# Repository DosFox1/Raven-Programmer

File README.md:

# Raven-Programmer
An implementation of a 68HC705E1 Programmer, to replace the 68HC05E1 Mask ROM Microcontroller that was used as the EGRET and CUDA ICs in 90s Macintoshes, with the EPROM programmable 68HC705E1 part. 

The EGRET and CUDA were used to implement the RTC, PRAM, Soft Power and other functions. As these are located near to the RTC battery, these are well known to be destroyed either by battery leaks or due to capacitor leaks.

The EGRET replacement has been confirmed to work. Many thanks to Max1zzz for testing them.

# How do I use it?

Unfortunately, the programmer is a two step process.
 The first step is to program the desired ROM to a suitable 2764 compatible 8K E/EPROM, using a suitable programmer. (In my case, I used an AT28C64 with a TI866+).

Once programmed, the ROM and a blank 68HC705e1 can then be inserted into the Raven programmer.

First, set switch 1 to on, and switch 2 to off. 
This will set the programmer into “validation” mode.
Bring the 5v rail up first before bringing the 16v programming rail up. 
Bringing the 16v rail up before the 5v rail may result in damage tom the IC. 
When both rails are stable, hit the reset button. 
Note that the 68HC705 will not enter boot loader mode until both power rails are present.

If the device has not been programmed before, neither the program or verify LEDs will light. 

Once satisfied that the 68HC705e1 is likely to be unprogrammed, set both switch 1 and 2 to “on”, and hit the reset button. 
This will set the programmer into program mode. 
At this point, the programmer will begin copying the contents of the external ROM into the onboard ROM of the 68HC705e1.
During this, the “program” LED will become illuminated. 
This process should take approximately 40 seconds, wherein the “program” LED will be extinguished, and the “verify” LED will become illuminated - to indicate that programming was successful.
If there is an issue - the “verify” LED will not become illuminated. 

To ensure that programming was a success, power cycle the setup (whilst ensuring that the 16v rail is powered down first, and powered up first), and set switch 1 to “on” and switch 2 to “off”. 
Again, this will set the programmer into verify mode - however, when the reset LED is hit in this instant, the “verify” LED should become illuminated after a second. 

Once satisfied, power down the programmer, and remove the 68HC705. 

# Where do I get the ROMs? 
At the moment, there is only a single ROM available in the correct format for the Raven programmer. This is the 341S0851 EGRET, that is a commonly used replacement for the majority of the EGRETs. 

The original program data was taken from the internet archive: 
https://archive.org/details/macroms

Which is likely taken from this tool here for dumping EGRET/CUDA ROMs:
https://www.gryphel.com/c/minivmac/extras/egretrom/

These ROMs have been used with a 68HC05 emulator within MAME, so it is likely the data is valid data. 

However, please note that there is some formatting that needs to take place before the ROM files can be burnt to the external 8K EPROM. 

Namely, the program data needs to be offset from 0x0000 to 0x0F00. This program data is 4096 bytes long, and resides from 0x0F00 to 0x1EFF. 

Following this, there needs to be single byte written at 0x1F00 - which is the Mask Option Register. 
From what we can tell, this data is usually part of the mask of the 68HC05e1 itself, and as a result needs to be defined in the 68HC705. As the data from 0x1F00 through to 0x1FEF is the bootloader ROM on the 68HC05e1, and the dumps include the entire bootloader ROM for the EGRET and CUDA, then writing the data from 0x1F00 from the dump will not work. 
Instead, MOR needs to be defined from context clues. 

The MOR defines three things - whether the watchdog is enable, if an external interrupt is enabled, and the rate of the internal interrupt.
In the case of the EGRET, the NMI pin is always held high - meaning it’s likely the external interrupt is not used. According to a decompilation by PhilPem, the Watchdog timer is not used. 
As the EGRET is also used as an RTC, it’s likely that the internal interrupt is 1s long. As a result, 0x1F00 should have the byte “0x04” written to it.

It’s hoped that even if the internal interrupt is wrong, then the clock will just run slightly slow - which can be easily fixed by burning a new EGRET. 

The data from 0x1F01 through to 0x1FEF should then be set to 0x00, as this is the region where the bootloader resides. It’s safer to null out this data region to avoid possibly corrupting the 68hc705e1. 

Finally, the last 16 bytes from 0x1FF0 through to 0x1FFF are the EPROM user vectors, that need to be copied from the original ROM. 

Additionally, there is an errata sheet (included) that details a bug with the exact mask version of the 68HC705 that I have programmed (D32N). Basically a silicon bug means that the 68HC705e1 doesn’t read the data at 0x1000, and reads the data at 0x0000 for a single cycle. This is why the included example ROM has a single byte of 0x12 at 0x0000 - this is a duplication of the data at 0x1000. It does not harm or hinder to have this additional byte present at 0x0000. 

Additional correctly formatted ROMs will be added if and when they are needed. 
Contact me directly for a specific ROM.

# Errata
VDEV2 is the current version of the Raven Programmer. The VDEV1 version had two issues - one introduced by me, the other by NXP. 
The issue I managed to introduce was accidentally mislabelling R1 and R2. I managed to get the 330K and 20M labels the wrong way around. This resulted in the oscillator not running, and was fixed in VDEV2. 

The major issue was introduced by NXP, who in their datasheet (68hc705e1.pdf in the datasheet folder) failed to mention that PB1 needed to be brought high to 5v, and PB6/PB7 needed to be brought low to 0v. As a result, with those three pins floating, the 68HC705e1 behaved erratically and failed to program. In this instant, both the verify and program LEDs remained illuminated.

Thankfully, the discovery of the original Motorola datasheet (68HC705e1 Better Datasheet.pdf), I was able to correct the issue, and actually program the devices.

# Acknowledgements 

Many thanks to PhilPem (@philpem@digipres.club) for helping with the software side of this headache, hopefully they work!

Also many thanks must be given to Max1zzz (https://github.com/max234252/) for agreeing to testing this new batch of EGRETs. We can only help that these will work, as well as agreeing to send an OTP CUDA over, so we can hopefully have a look at what a proper MOR byte should look like!

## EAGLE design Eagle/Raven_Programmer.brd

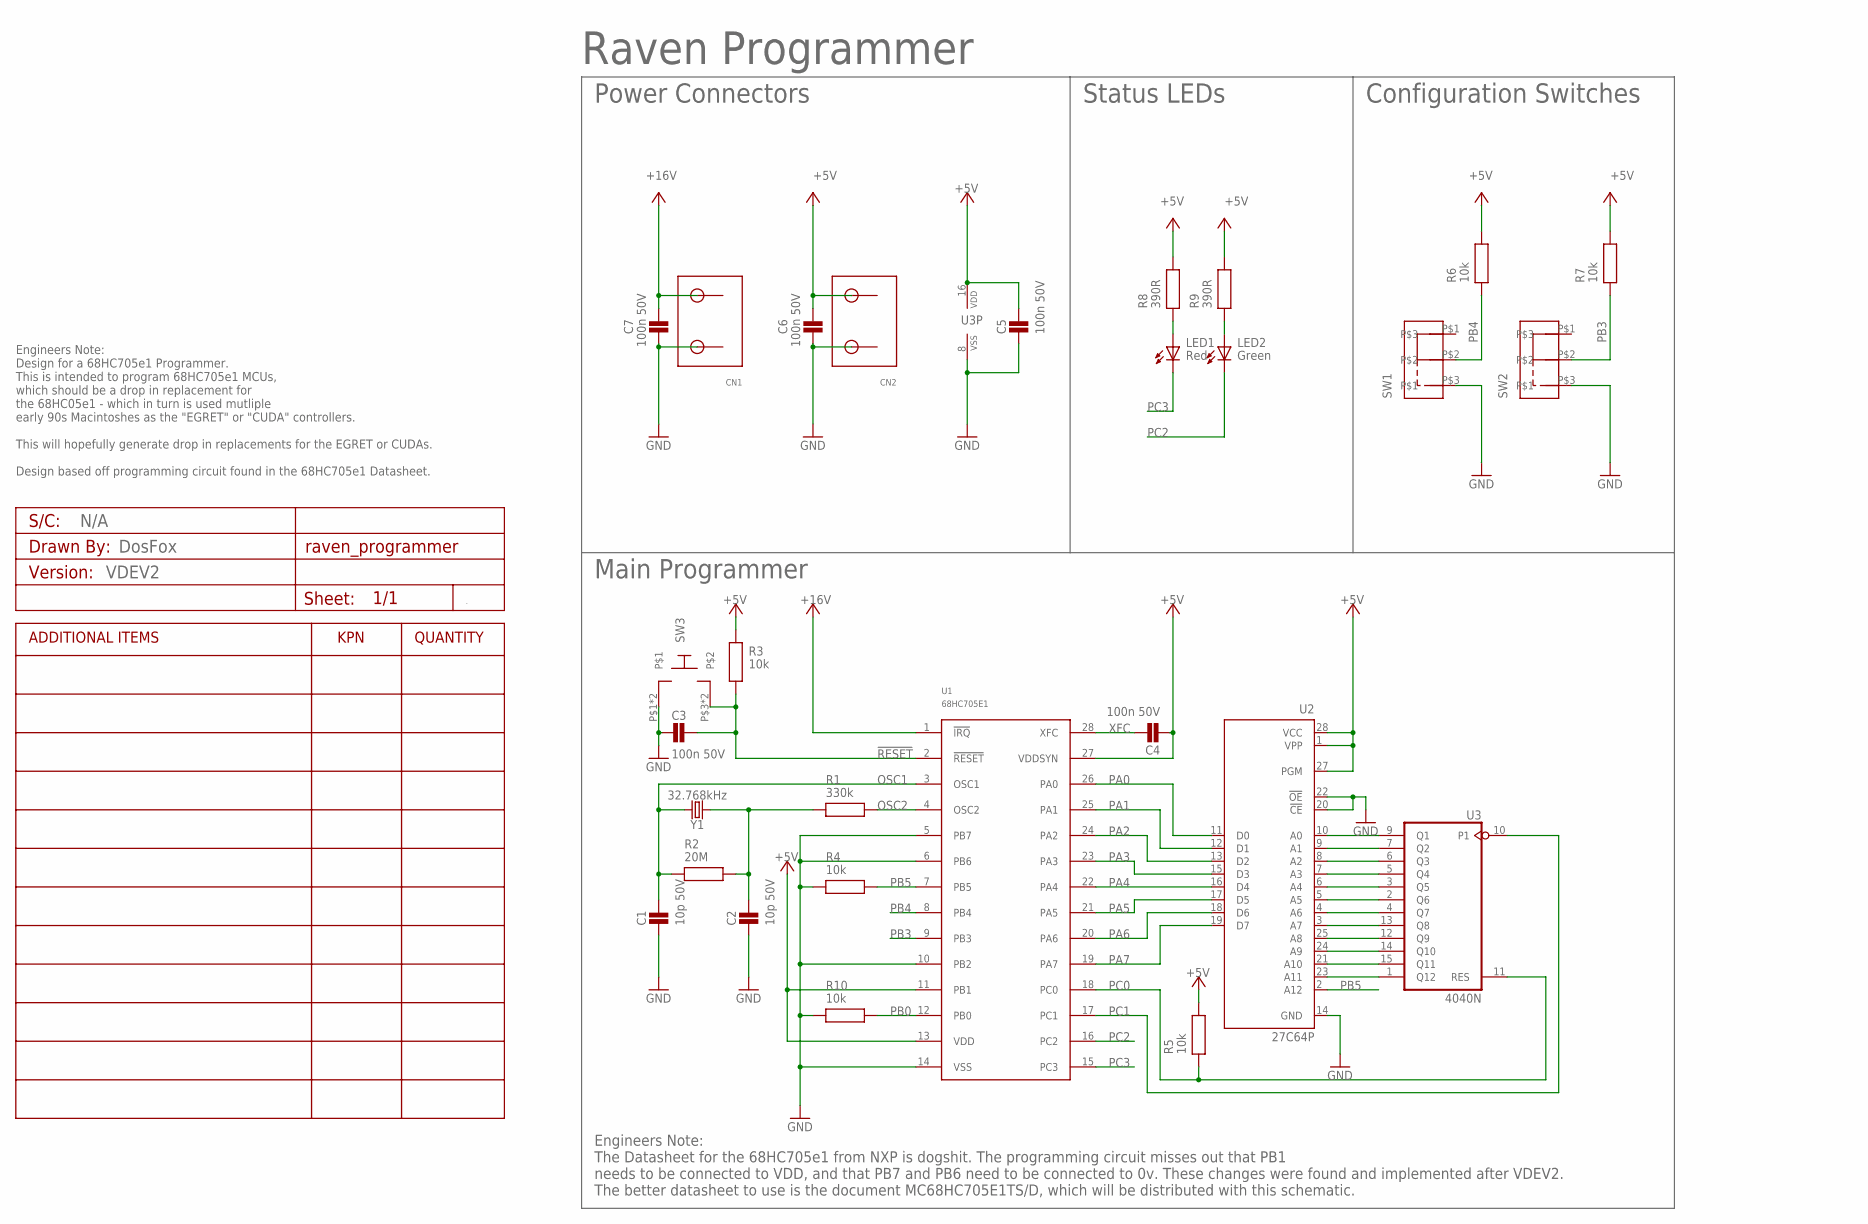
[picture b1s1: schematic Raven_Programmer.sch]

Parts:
A1: VDEV2; PCB_CUSTOM_DETAILS
C1, C2: 10p 50V; CAP_5.08MM_PITCH
C3, C4, C5, C6, C7: 100n 50V; CAP_5.08MM_PITCH
CN1, CN2: VTB301V-2P-B; TERMINALBLOCK2WAY
LED1: Red; 5MM_TH_VERT_STANDARD
LED2: Green; 5MM_TH_VERT_STANDARD
R1: 330k; RESISTORTHRUHOLE
R2: 20M; RESISTORTHRUHOLE
R3, R4, R5, R6, R7, R10: 10k; RESISTORTHRUHOLE
R8, R9: 390R; RESISTORTHRUHOLE
SW1, SW2: SK12D07_SLIDE_SWITCH
SW3: DTS-61; DIP_DTS_6_TACT_SWITCH_6X6_TH
U1: 68HC705E1; DIP28
U2: 27C64P; DIL28-6
U3: 4040N; DIL16
Y1: 32.768kHz; CRYSTAL-PTH-2X6-CYL

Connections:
!RESET: C3.P$2, R3.P$1, SW3.P$3, SW3.P$4, U1.2 (!RESET)
+5V: C4.P$1, C5.P$2, C6.P$2, CN2.P$2, R3.P$2, R5.P$2, R6.P$2, R7.P$2, R8.P$2, R9.P$2, U1.11 (PB1), U1.13 (VDD), U1.27 (VDDSYN), U2.1 (VPP), U2.27 (PGM), U2.28 (VCC), U3.16 (VDD)
+16V: C7.P$2, CN1.P$2, U1.1 (!IRQ)
GND: C1.P$1, C2.P$1, C3.P$1, C5.P$1, C6.P$1, C7.P$1, CN1.P$1, CN2.P$1, R4.P$1, R10.P$1, SW1.P$3, SW2.P$3, SW3.P$1, SW3.P$2, U1.5 (PB7), U1.6 (PB6), U1.10 (PB2), U1.14 (VSS), U2.14 (GND), U2.20 (!CE), U2.22 (!OE), U3.8 (VSS)
unnamed: U2.10 (A0), U3.9 (Q1)
unnamed: U2.9 (A1), U3.7 (Q2)
unnamed: U2.8 (A2), U3.6 (Q3)
unnamed: U2.7 (A3), U3.5 (Q4)
unnamed: U2.6 (A4), U3.3 (Q5)
unnamed: U2.4 (A6), U3.4 (Q7)
unnamed: U2.5 (A5), U3.2 (Q6)
unnamed: U2.3 (A7), U3.13 (Q8)
unnamed: U2.25 (A8), U3.12 (Q9)
unnamed: U2.24 (A9), U3.14 (Q10)
unnamed: U2.21 (A10), U3.15 (Q11)
unnamed: U2.23 (A11), U3.1 (Q12)
unnamed: C2.P$2, R1.P$1, R2.P$2, Y1.1
unnamed: LED1.A, R8.P$1
unnamed: LED2.A, R9.P$1
OSC1: C1.P$2, R2.P$1, U1.3 (OSC1), Y1.2
OSC2: R1.P$2, U1.4 (OSC2)
PA0: U1.26 (PA0), U2.11 (D0)
PA1: U1.25 (PA1), U2.12 (D1)
PA2: U1.24 (PA2), U2.13 (D2)
PA3: U1.23 (PA3), U2.15 (D3)
PA4: U1.22 (PA4), U2.16 (D4)
PA5: U1.21 (PA5), U2.17 (D5)
PA6: U1.20 (PA6), U2.18 (D6)
PA7: U1.19 (PA7), U2.19 (D7)
PB0: R10.P$2, U1.12 (PB0)
PB3: R7.P$1, SW2.P$2, U1.9 (PB3)
PB4: R6.P$1, SW1.P$2, U1.8 (PB4)
PB5: R4.P$2, U1.7 (PB5), U2.2 (A12)
PC0: R5.P$1, U1.18 (PC0), U3.11 (RES)
PC1: U1.17 (PC1), U3.10 (P1)
PC2: LED2.C, U1.16 (PC2)
PC3: LED1.C, U1.15 (PC3)
XFC: C4.P$2, U1.28 (XFC)

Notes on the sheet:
Raven Programmer
Power Connectors
Status LEDs
Configuration Switches
Main Programmer
DosFox
N/A
Engineers Note: Design for a 68HC705e1 Programmer. This is intended to program 68HC705e1 MCUs, which should be a drop in replacement for the 68HC05e1 - which in turn is used mutliple early 90s Macintoshes as the "EGRET" or "CUDA" controllers. This will hopefully generate drop in replacements for th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
Engineers Note: The Datasheet for the 68HC705e1 from NXP is dogshit. The programming circuit misses out that PB1 needs to be connected to VDD, and that PB7 and PB6 need to be connected to 0v. These changes were found and implemented after VDEV2. The better datasheet to use is the document MC68HC705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

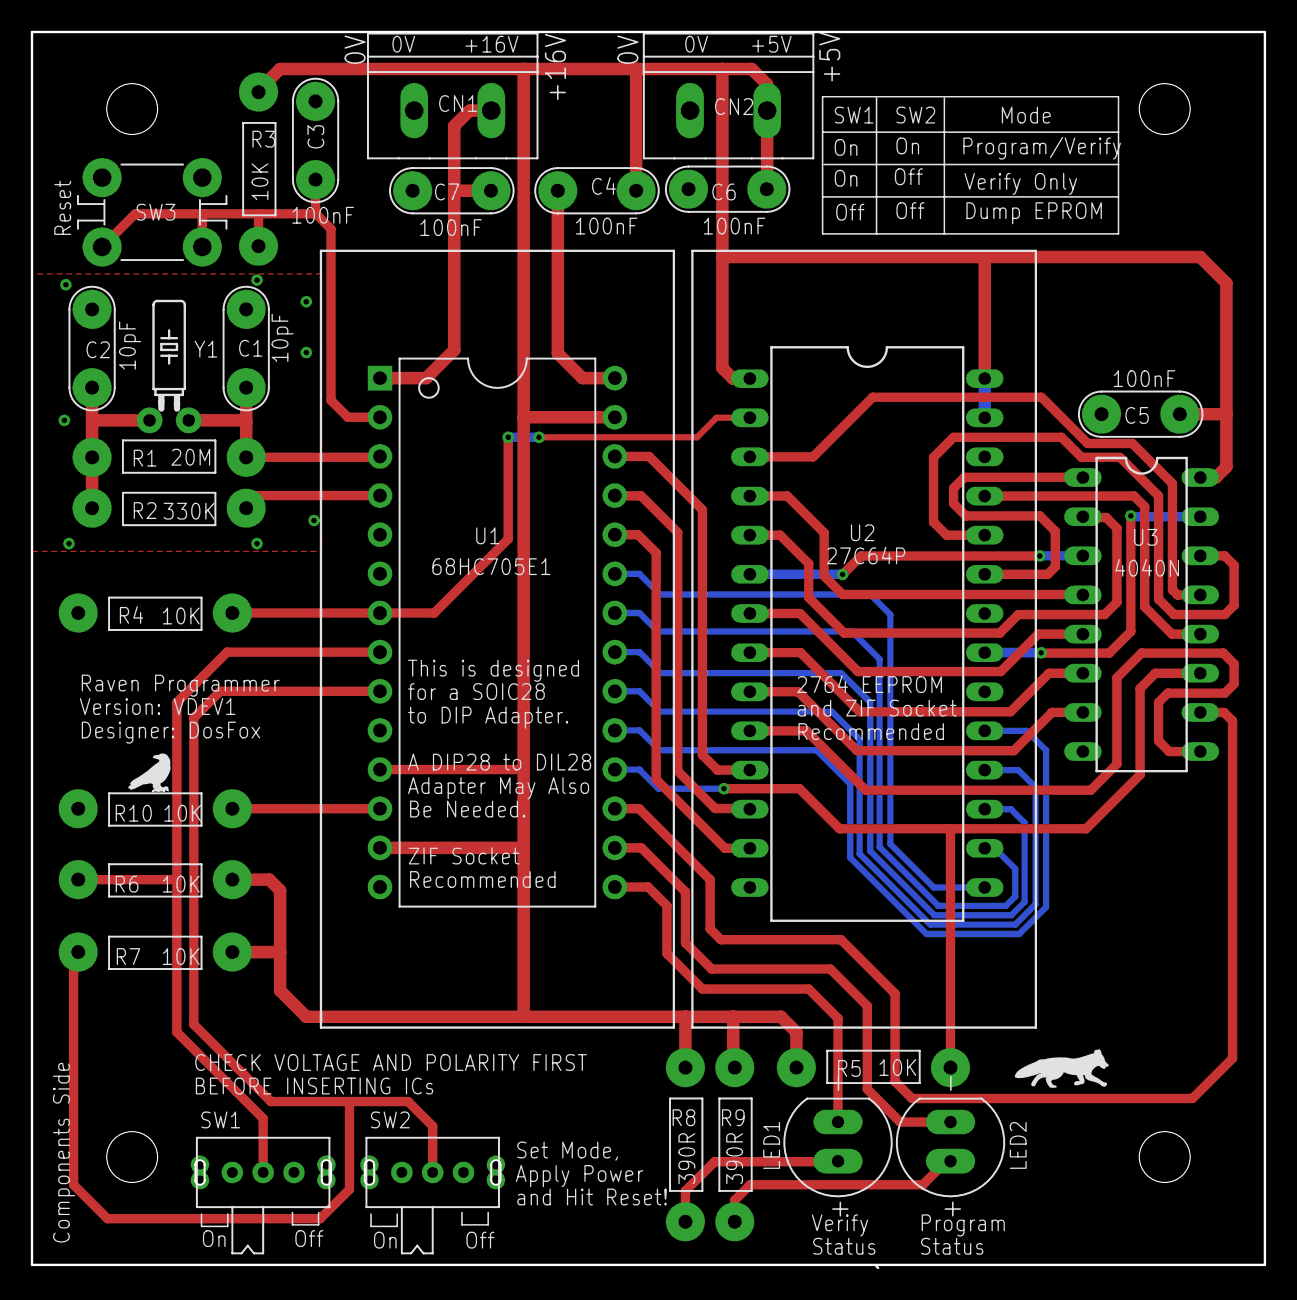
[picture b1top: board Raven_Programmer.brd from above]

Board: 2 copper layers, 80.0 x 80.0 mm, 29 parts (0 on the bottom side), 38 nets.

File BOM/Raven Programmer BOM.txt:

Partlist

Assembly variant: 

Part     Value          Device                   Package                      Library         Sheet

C1       10p 50V        10pF_TH_CAP              CAP_5.08MM_PITCH             Capacitors TH   1
C2       10p 50V        10pF_TH_CAP              CAP_5.08MM_PITCH             Capacitors TH   1
C3       100n 50V       100N_TH_CAP              CAP_5.08MM_PITCH             Capacitors TH   1
C4       100n 50V       100N_TH_CAP              CAP_5.08MM_PITCH             Capacitors TH   1
C5       100n 50V       100N_TH_CAP              CAP_5.08MM_PITCH             Capacitors TH   1
C6       100n 50V       100N_TH_CAP              CAP_5.08MM_PITCH             Capacitors TH   1
C7       100n 50V       100N_TH_CAP              CAP_5.08MM_PITCH             Capacitors TH   1
CN1      VTB301V-2P-B   TERMINALBLOCK2WAY        TERMINALBLOCK2WAY            Connectors      1
CN2      VTB301V-2P-B   TERMINALBLOCK2WAY        TERMINALBLOCK2WAY            Connectors      1
LED1     Red            5MM_LED_RED              5MM_TH_VERT_STANDARD         Optoelectronics 1
LED2     Green          5MM_LED_GREEN            5MM_TH_VERT_STANDARD         Optoelectronics 1
R1       330k           330K_TH_RESISTOR         RESISTORTHRUHOLE             Resistors TH    1
R2       20M            20M_TH_RESISTOR          RESISTORTHRUHOLE             Resistors TH    1
R3       10k            10K_TH_RESISTOR          RESISTORTHRUHOLE             Resistors TH    1
R4       10k            10K_TH_RESISTOR          RESISTORTHRUHOLE             Resistors TH    1
R5       10k            10K_TH_RESISTOR          RESISTORTHRUHOLE             Resistors TH    1
R6       10k            10K_TH_RESISTOR          RESISTORTHRUHOLE             Resistors TH    1
R7       10k            10K_TH_RESISTOR          RESISTORTHRUHOLE             Resistors TH    1
R8       390R           390R_TH_RESISTOR         RESISTORTHRUHOLE             Resistors TH    1
R9       390R           390R_TH_RESISTOR         RESISTORTHRUHOLE             Resistors TH    1
R10      10k            10K_TH_RESISTOR          RESISTORTHRUHOLE             Resistors TH    1
SW1      SPDT           SK12D07_SLIDE_SWITCH     SK12D07_SLIDE_SWITCH         Switches        1
SW2      SPDT           SK12D07_SLIDE_SWITCH     SK12D07_SLIDE_SWITCH         Switches        1
SW3      DTS-61         DIP_TACT_SWITCH_6X6TH    DIP_DTS_6_TACT_SWITCH_6X6_TH Switches        1
U1       68HC705E1      68HC705E1                DIP28 Adapter                CN1             1
U2       27C64P         27C64P                   DIL28-6                      microchip       1
U3       74HCT4040N     74HCT4040N               DIL16                        40xx            1
Y1       32.768kHz      CRYSTAL-32.768KHZPTH-2X6 CRYSTAL-PTH-2X6-CYL          SparkFun-Clocks 1

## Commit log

2024-10-21 Create License
2024-11-02 Add files via upload
    Cuda Lite as found from a Tanzania based board. This is only here for reference

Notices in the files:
parts and their libraries:
SparkFun-Clocks: Licensing: Creative Commons ShareAlike 4.0 International - https://creativecommons.org/licenses/by-sa/4.0
